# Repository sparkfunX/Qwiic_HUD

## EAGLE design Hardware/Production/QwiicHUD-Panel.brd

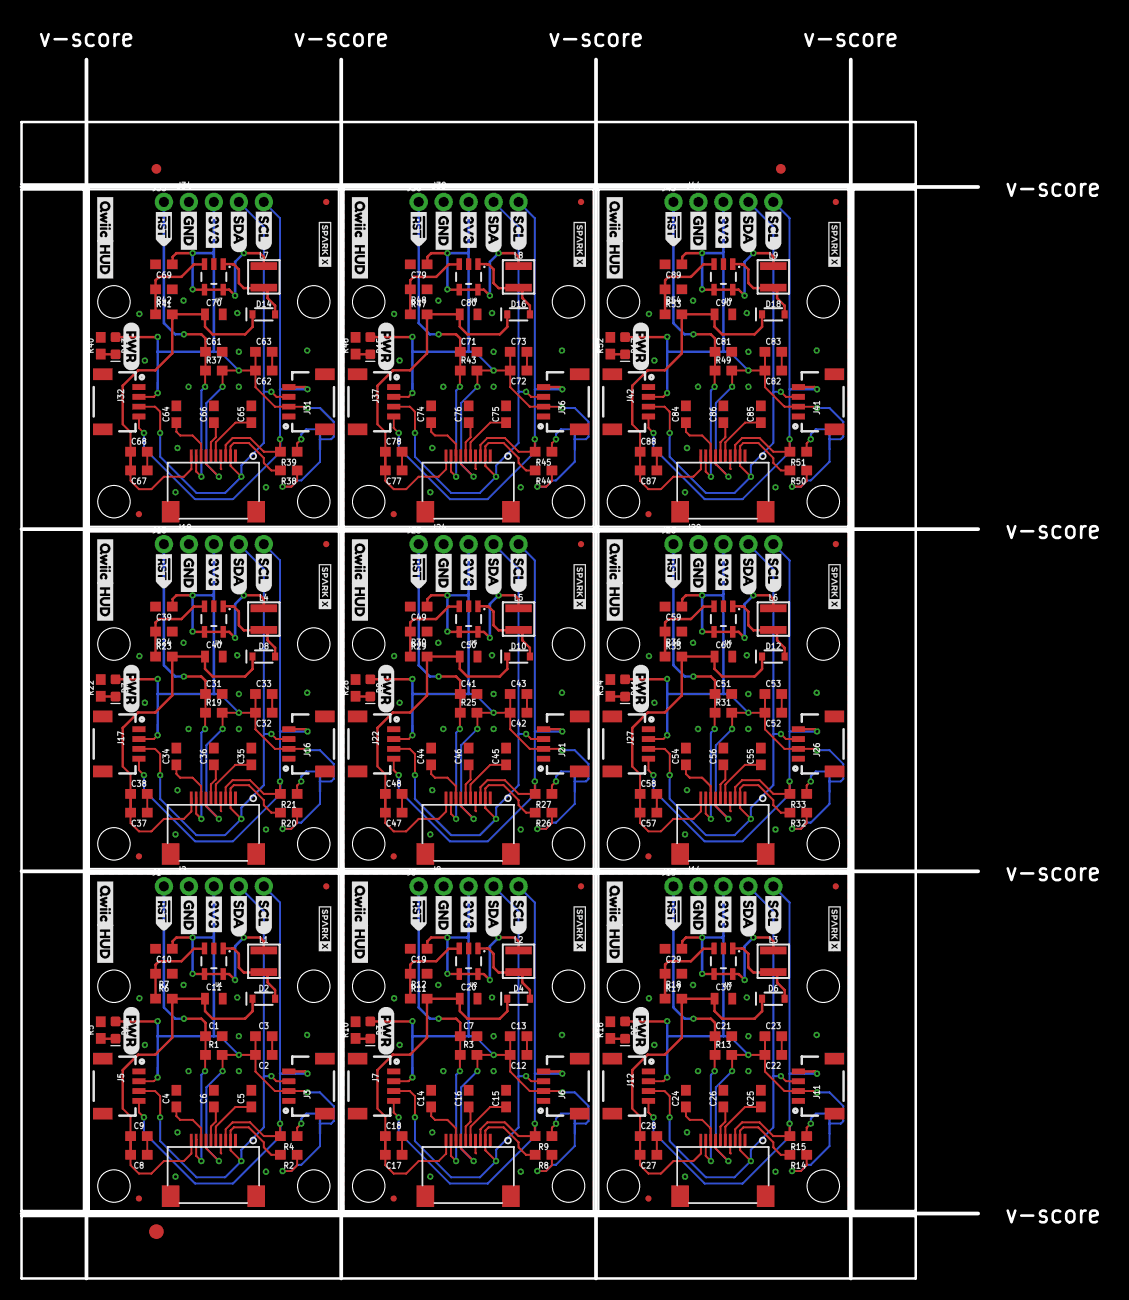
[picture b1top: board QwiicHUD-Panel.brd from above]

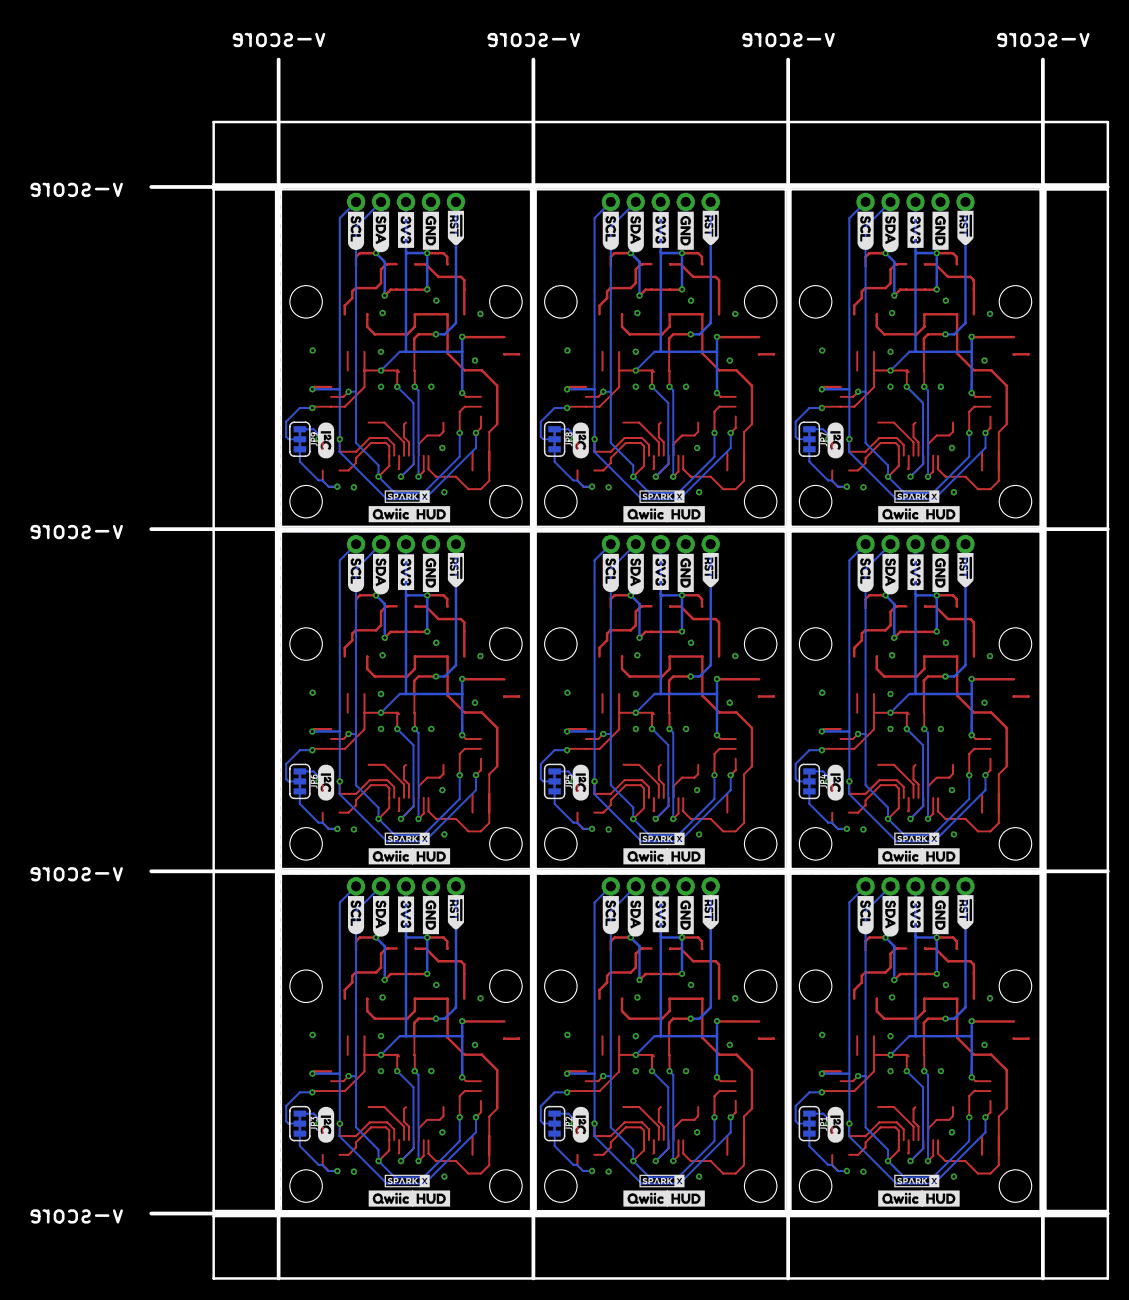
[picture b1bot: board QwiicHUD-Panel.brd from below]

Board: 2 copper layers, 110.5 x 127.8 mm, 426 parts (90 on the bottom side), 126 nets.

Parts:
C1, C7, C21, C31, C41, C51, C61, C71, C81: 2.2uF; 0603
C2, C8, C12, C17, C22, C27, C32, C37, C42, C47, C52, C57, C62, C67, C72, C77, C82, C87: 4.7uF; 0603
C3, C9, C13, C18, C23, C28, C33, C38, C43, C48, C53, C58, C63, C68, C73, C78, C83, C88: 0.1uF; 0603
C4, C5, C6, C10, C14, C15, C16, C19, C24, C25, C26, C29, C34, C35, C36, C39, C44, C45, C46, C49, C54, C55, C56, C59, C64, C65, C66, C69, C74, C75, C76, C79, C84, C85, C86, C89: 1.0uF; 0603
C11, C20, C30, C40, C50, C60, C70, C80, C90: 1.0uF/25V; 0805
D1, D3, D5, D7, D9, D11, D13, D15, D17: RED; LED-0603
D2, D4, D6, D8, D10, D12, D14, D16, D18: 1A/23V/620mV; SOD-323
E$1, E$2: FIDUCIAL-1X2
E$3: FIDUCIAL-1.5X3
FD1, FD2, FD3, FD4, FD5, FD6, FD7, FD8, FD9, FD10, FD11, FD12, FD13, FD14, FD15, FD16, FD17, FD18: FIDUCIALUFIDUCIAL; FIDUCIAL-MICRO
J1, J8, J13, J18, J23, J28, J33, J38, J43: 1X01_NO_SILK
J2, J9, J14, J19, J24, J29, J34, J39, J44: 1X04_NO_SILK
J3, J5, J6, J7, J11, J12, J16, J17, J21, J22, J26, J27, J31, J32, J36, J37, J41, J42: 1X04_1MM_RA
J4, J10, J15, J20, J25, J30, J35, J40, J45: WISECHIP_HUD_FPC; SERIES6288
JP1, JP2, JP3, JP4, JP5, JP6, JP7, JP8, JP9: SMT-JUMPER_3_2-NC_TRACE_SILK
L1, L2, L3, L4, L5, L6, L7, L8, L9: 10uH; INDUCTOR_3X3
R1, R3, R13, R19, R25, R31, R37, R43, R49: 10k; 0603
R2, R4, R8, R9, R14, R15, R20, R21, R26, R27, R32, R33, R38, R39, R44, R45, R50, R51: 2.2k; 0603
R5, R10, R16, R22, R28, R34, R40, R46, R52: 1k; 0603
R6, R11, R17, R23, R29, R35, R41, R47, R53: 47k; 0603
R7, R12, R18, R24, R30, R36, R42, R48, R54: 5.6k; 0603
U1, U2, U3, U4, U5, U6, U7, U8, U9: AP3012; SOT23-5
U$1, U$14, U$23, U$33, U$42, U$52, U$61, U$71, U$80, U$90, U$99, U$109, U$118, U$128, U$137, U$147, U$156, U$166: #RST>
U$2, U$15, U$39, U$58, U$77, U$96, U$115, U$134, U$153: QWIIC_BOARD_OUTLINEH; QWIIC_BOARD_MOUNT_HOLES
U$3, U$4, U$21, U$22, U$40, U$41, U$59, U$60, U$78, U$79, U$97, U$98, U$116, U$117, U$135, U$136, U$154, U$155: SPARKX-TINY
U$5, U$13, U$24, U$32, U$43, U$51, U$62, U$70, U$81, U$89, U$100, U$108, U$119, U$127, U$138, U$146, U$157, U$165: GND
U$6, U$12, U$25, U$31, U$44, U$50, U$63, U$69, U$82, U$88, U$101, U$107, U$120, U$126, U$139, U$145, U$158, U$164: 3V3
U$7, U$10, U$26, U$29, U$45, U$48, U$64, U$67, U$83, U$86, U$102, U$105, U$121, U$124, U$140, U$143, U$159, U$162: SDA
U$8, U$11, U$27, U$30, U$46, U$49, U$65, U$68, U$84, U$87, U$103, U$106, U$122, U$125, U$141, U$144, U$160, U$163: SCL
U$9, U$28, U$47, U$66, U$85, U$104, U$123, U$142, U$161: (PWR)
U$16, U$18, U$34, U$36, U$53, U$55, U$72, U$74, U$91, U$93, U$110, U$112, U$129, U$131, U$148, U$150, U$167, U$169: QWIIC0
U$17, U$19, U$35, U$37, U$54, U$56, U$73, U$75, U$92, U$94, U$111, U$113, U$130, U$132, U$149, U$151, U$168, U$170: HUD1
U$20, U$38, U$57, U$76, U$95, U$114, U$133, U$152, U$171: (I_SUPER2_C)

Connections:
3.3V: C2.2, C3.1, C10.1, D1.A, J2.2, J3.2, J4.4, J5.2, JP1.2, L1.P$1, R1.2, U1.4, U1.5
3.3V1: C12.2, C13.1, C19.1, D3.A, J6.2, J7.2, J9.2, J10.4, JP2.2, L2.P$1, R3.2, U2.4, U2.5
3.3V2: C22.2, C23.1, C29.1, D5.A, J11.2, J12.2, J14.2, J15.4, JP3.2, L3.P$1, R13.2, U3.4, U3.5
3.3V3: C32.2, C33.1, C39.1, D7.A, J16.2, J17.2, J19.2, J20.4, JP4.2, L4.P$1, R19.2, U4.4, U4.5
3.3V4: C42.2, C43.1, C49.1, D9.A, J21.2, J22.2, J24.2, J25.4, JP5.2, L5.P$1, R25.2, U5.4, U5.5
3.3V5: C52.2, C53.1, C59.1, D11.A, J26.2, J27.2, J29.2, J30.4, JP6.2, L6.P$1, R31.2, U6.4, U6.5
3.3V6: C62.2, C63.1, C69.1, D13.A, J31.2, J32.2, J34.2, J35.4, JP7.2, L7.P$1, R37.2, U7.4, U7.5
3.3V7: C72.2, C73.1, C79.1, D15.A, J36.2, J37.2, J39.2, J40.4, JP8.2, L8.P$1, R43.2, U8.4, U8.5
3.3V8: C82.2, C83.1, C89.1, D17.A, J41.2, J42.2, J44.2, J45.4, JP9.2, L9.P$1, R49.2, U9.4, U9.5
12V: C8.2, C9.1, C11.1, D2.C, J4.1, R6.2
12V1: C17.2, C18.1, C20.1, D4.C, J10.1, R11.2
12V2: C27.2, C28.1, C30.1, D6.C, J15.1, R17.2
12V3: C37.2, C38.1, C40.1, D8.C, J20.1, R23.2
12V4: C47.2, C48.1, C50.1, D10.C, J25.1, R29.2
12V5: C57.2, C58.1, C60.1, D12.C, J30.1, R35.2
12V6: C67.2, C68.1, C70.1, D14.C, J35.1, R41.2
12V7: C77.2, C78.1, C80.1, D16.C, J40.1, R47.2
12V8: C87.2, C88.1, C90.1, D18.C, J45.1, R53.2
!RST: C1.1, J1.1, J4.2, R1.1
!RST1: C7.1, J8.1, J10.2, R3.1
!RST2: C21.1, J13.1, J15.2, R13.1
!RST3: C31.1, J18.1, J20.2, R19.1
!RST4: C41.1, J23.1, J25.2, R25.1
!RST5: C51.1, J28.1, J30.2, R31.1
!RST6: C61.1, J33.1, J35.2, R37.1
!RST7: C71.1, J38.1, J40.2, R43.1
!RST8: C81.1, J43.1, J45.2, R49.1
GND: C1.2, C2.1, C3.2, C4.2, C5.2, C6.2, C8.1, C9.2, C10.2, C11.2, J2.1, J3.1, J4.7, J4.10, J5.1, R5.2, R7.1, U1.2
GND1: C7.2, C12.1, C13.2, C14.2, C15.2, C16.2, C17.1, C18.2, C19.2, C20.2, J6.1, J7.1, J9.1, J10.7, J10.10, R10.2, R12.1, U2.2
GND2: C21.2, C22.1, C23.2, C24.2, C25.2, C26.2, C27.1, C28.2, C29.2, C30.2, J11.1, J12.1, J14.1, J15.7, J15.10, R16.2, R18.1, U3.2
GND3: C31.2, C32.1, C33.2, C34.2, C35.2, C36.2, C37.1, C38.2, C39.2, C40.2, J16.1, J17.1, J19.1, J20.7, J20.10, R22.2, R24.1, U4.2
GND4: C41.2, C42.1, C43.2, C44.2, C45.2, C46.2, C47.1, C48.2, C49.2, C50.2, J21.1, J22.1, J24.1, J25.7, J25.10, R28.2, R30.1, U5.2
GND5: C51.2, C52.1, C53.2, C54.2, C55.2, C56.2, C57.1, C58.2, C59.2, C60.2, J26.1, J27.1, J29.1, J30.7, J30.10, R34.2, R36.1, U6.2
GND6: C61.2, C62.1, C63.2, C64.2, C65.2, C66.2, C67.1, C68.2, C69.2, C70.2, J31.1, J32.1, J34.1, J35.7, J35.10, R40.2, R42.1, U7.2
GND7: C71.2, C72.1, C73.2, C74.2, C75.2, C76.2, C77.1, C78.2, C79.2, C80.2, J36.1, J37.1, J39.1, J40.7, J40.10, R46.2, R48.1, U8.2
GND8: C81.2, C82.1, C83.2, C84.2, C85.2, C86.2, C87.1, C88.2, C89.2, C90.2, J41.1, J42.1, J44.1, J45.7, J45.10, R52.2, R54.1, U9.2
IC1: C6.1, J4.5
IC2: C5.1, J4.6
IC3: C4.1, J4.3
IC4: C14.1, J10.3
IC5: C16.1, J10.5
IC6: C15.1, J10.6
IC7: C24.1, J15.3
IC8: C26.1, J15.5
IC9: C25.1, J15.6
IC10: C34.1, J20.3
IC11: C36.1, J20.5
IC12: C35.1, J20.6
IC13: C44.1, J25.3
IC14: C46.1, J25.5
IC15: C45.1, J25.6
IC16: C54.1, J30.3
IC17: C56.1, J30.5
IC18: C55.1, J30.6
IC19: C64.1, J35.3
IC20: C66.1, J35.5
IC21: C65.1, J35.6
IC22: C74.1, J40.3
IC23: C76.1, J40.5
IC24: C75.1, J40.6
IC25: C84.1, J45.3
IC26: C86.1, J45.5
IC27: C85.1, J45.6
unnamed: JP1.3, R2.1
unnamed: JP1.1, R4.1
unnamed: D1.C, R5.1
unnamed: D2.A, L1.P$2, U1.1
unnamed: R6.1, R7.2, U1.3
unnamed: JP2.3, R8.1
unnamed: JP2.1, R9.1
unnamed: D3.C, R10.1
unnamed: D4.A, L2.P$2, U2.1
unnamed: R11.1, R12.2, U2.3
unnamed: JP3.3, R14.1
unnamed: JP3.1, R15.1
unnamed: D5.C, R16.1
unnamed: D6.A, L3.P$2, U3.1
unnamed: R17.1, R18.2, U3.3
unnamed: JP4.3, R20.1
unnamed: JP4.1, R21.1
unnamed: D7.C, R22.1
unnamed: D8.A, L4.P$2, U4.1
unnamed: R23.1, R24.2, U4.3
unnamed: JP5.3, R26.1
unnamed: JP5.1, R27.1
unnamed: D9.C, R28.1
unnamed: D10.A, L5.P$2, U5.1
unnamed: R29.1, R30.2, U5.3
unnamed: JP6.3, R32.1
unnamed: JP6.1, R33.1
unnamed: D11.C, R34.1
unnamed: D12.A, L6.P$2, U6.1
unnamed: R35.1, R36.2, U6.3
unnamed: JP7.3, R38.1
unnamed: JP7.1, R39.1
unnamed: D13.C, R40.1
unnamed: D14.A, L7.P$2, U7.1
unnamed: R41.1, R42.2, U7.3
unnamed: JP8.3, R44.1
unnamed: JP8.1, R45.1
unnamed: D15.C, R46.1
unnamed: D16.A, L8.P$2, U8.1
unnamed: R47.1, R48.2, U8.3
unnamed: JP9.3, R50.1
unnamed: JP9.1, R51.1
unnamed: D17.C, R52.1
unnamed: D18.A, L9.P$2, U9.1
unnamed: R53.1, R54.2, U9.3
SCL: J2.4, J3.4, J4.8, J5.4, R4.2
SCL1: J6.4, J7.4, J9.4, J10.8, R9.2
SCL2: J11.4, J12.4, J14.4, J15.8, R15.2
SCL3: J16.4, J17.4, J19.4, J20.8, R21.2
SCL4: J21.4, J22.4, J24.4, J25.8, R27.2
SCL5: J26.4, J27.4, J29.4, J30.8, R33.2
SCL6: J31.4, J32.4, J34.4, J35.8, R39.2
SCL7: J36.4, J37.4, J39.4, J40.8, R45.2
SCL8: J41.4, J42.4, J44.4, J45.8, R51.2
SDA: J2.3, J3.3, J4.9, J5.3, R2.2
SDA1: J6.3, J7.3, J9.3, J10.9, R8.2
SDA2: J11.3, J12.3, J14.3, J15.9, R14.2
SDA3: J16.3, J17.3, J19.3, J20.9, R20.2
SDA4: J21.3, J22.3, J24.3, J25.9, R26.2
SDA5: J26.3, J27.3, J29.3, J30.9, R32.2
SDA6: J31.3, J32.3, J34.3, J35.9, R38.2
SDA7: J36.3, J37.3, J39.3, J40.9, R44.2
SDA8: J41.3, J42.3, J44.3, J45.9, R50.2

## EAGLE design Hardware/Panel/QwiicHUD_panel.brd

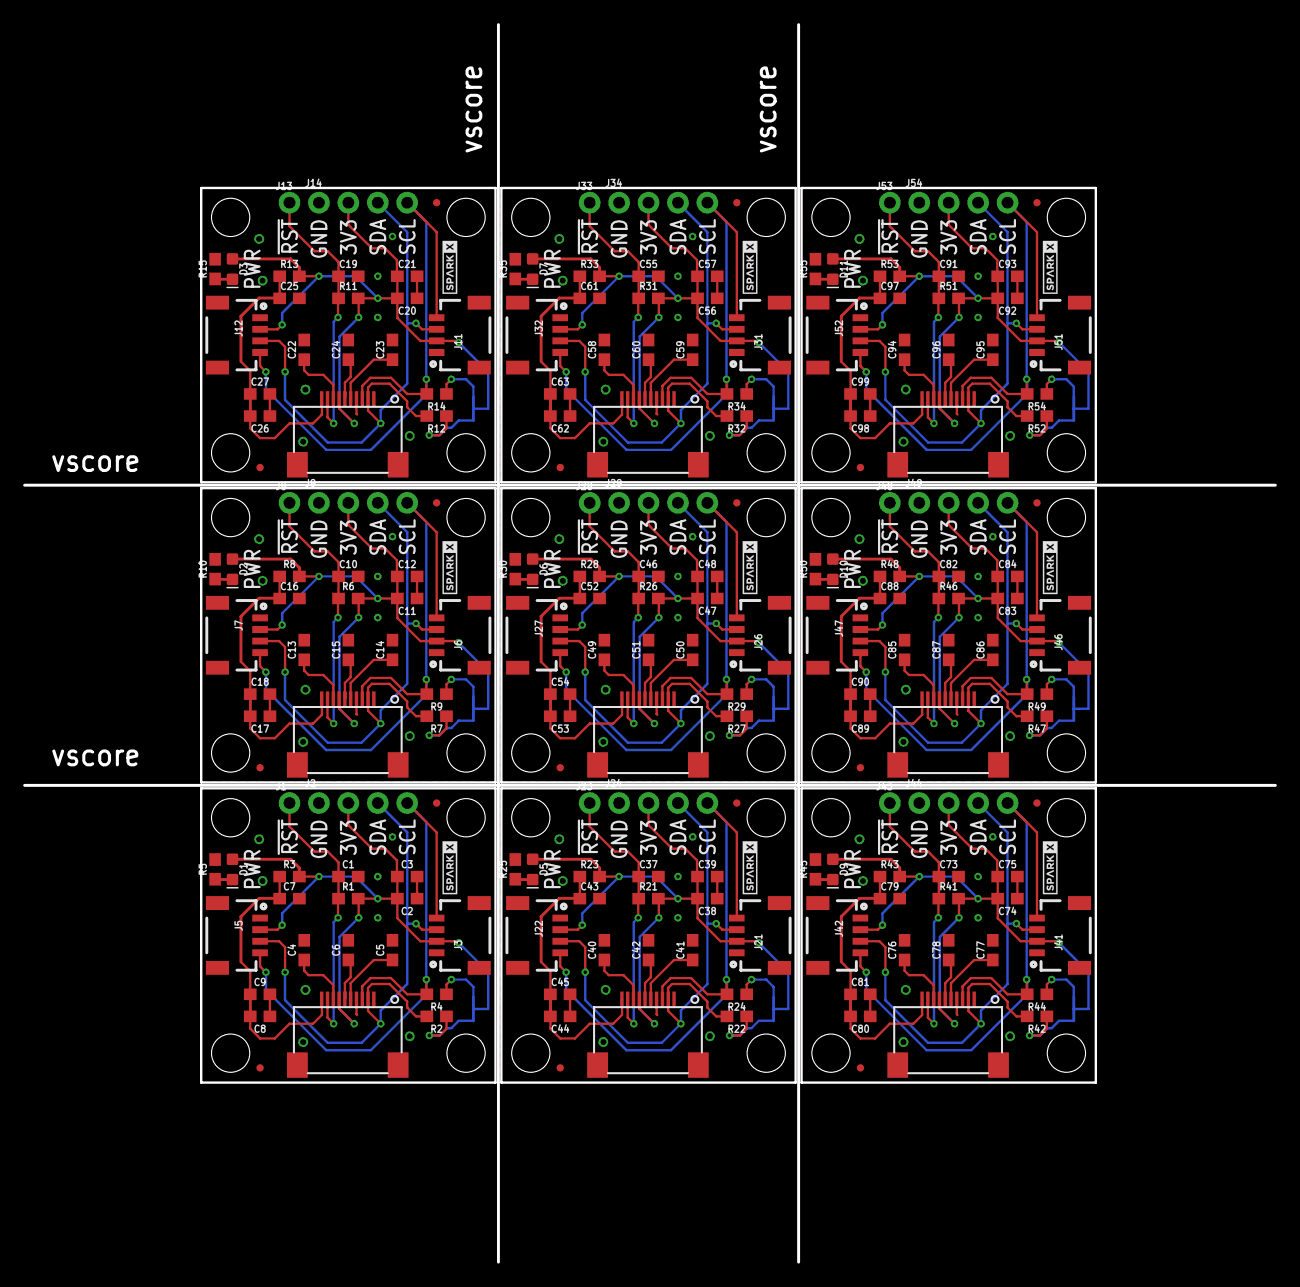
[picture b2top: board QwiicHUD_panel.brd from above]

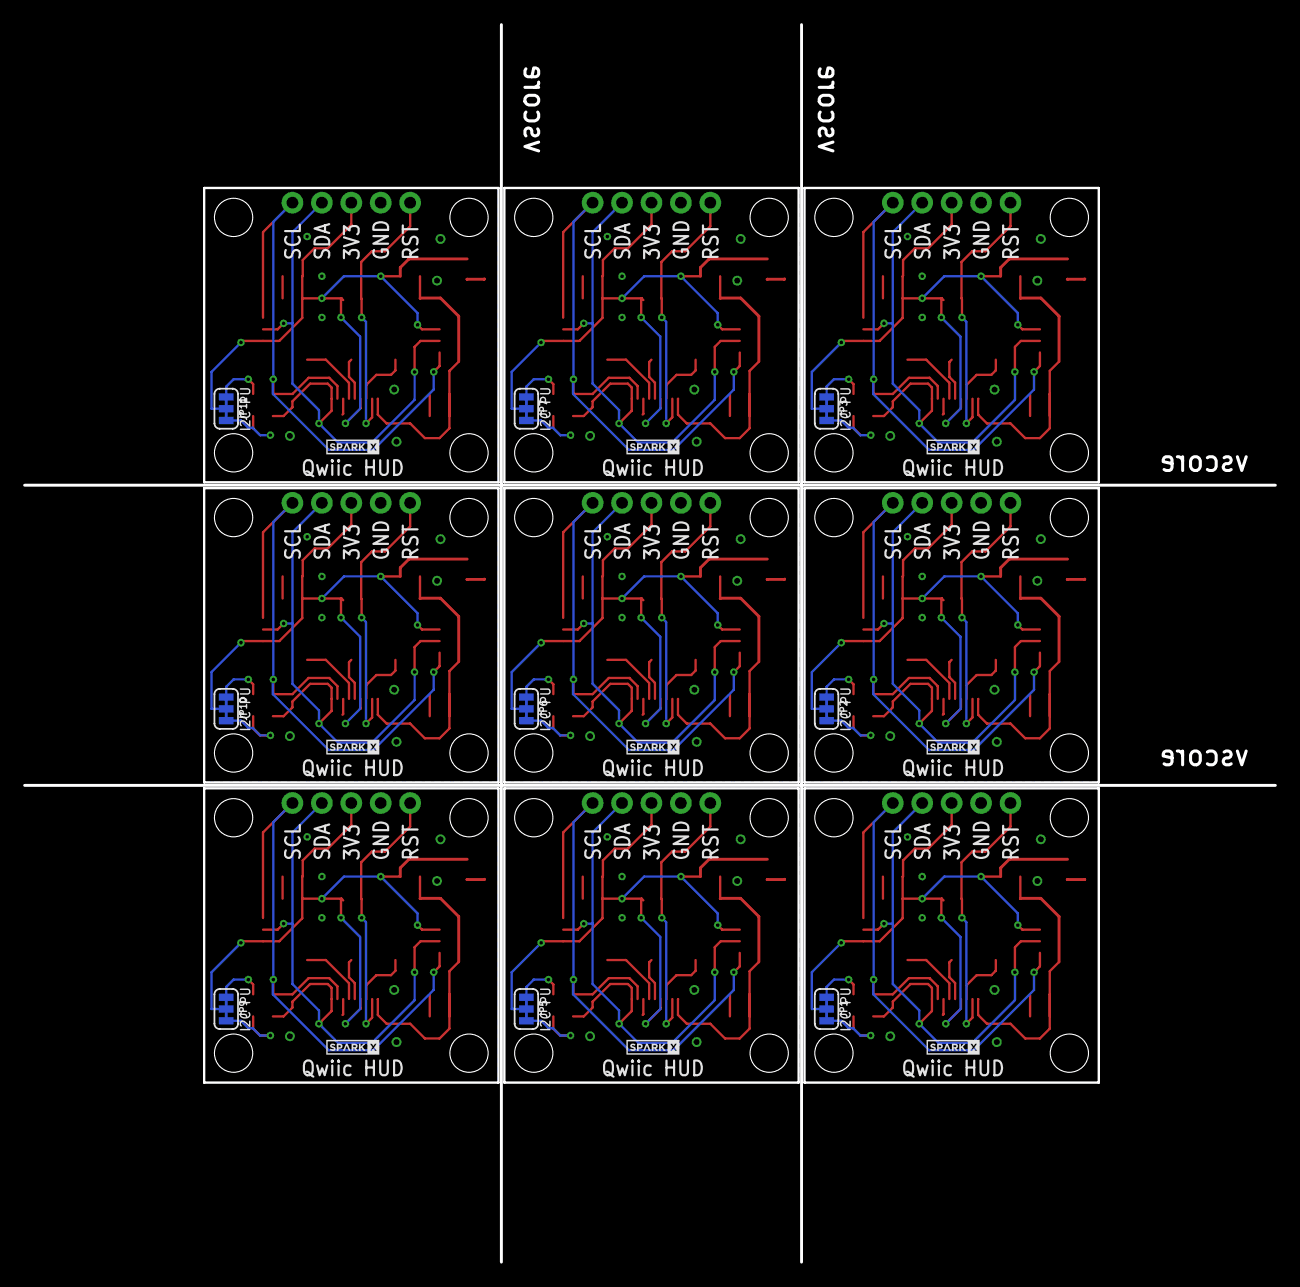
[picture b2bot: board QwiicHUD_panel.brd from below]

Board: 2 copper layers, 107.9 x 106.8 mm, 234 parts (18 on the bottom side), 108 nets.

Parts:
C1, C7, C10, C16, C19, C25, C37, C43, C46, C52, C55, C61, C73, C79, C82, C88, C91, C97: 2.2uF; 0603
C2, C8, C11, C17, C20, C26, C38, C44, C47, C53, C56, C62, C74, C80, C83, C89, C92, C98: 4.7uF; 0603
C3, C9, C12, C18, C21, C27, C39, C45, C48, C54, C57, C63, C75, C81, C84, C90, C93, C99: 0.1uF; 0603
C4, C5, C6, C13, C14, C15, C22, C23, C24, C40, C41, C42, C49, C50, C51, C58, C59, C60, C76, C77, C78, C85, C86, C87, C94, C95, C96: 1.0uF; 0603
D1, D2, D3, D5, D6, D7, D9, D10, D11: RED; LED-0603
FD1, FD2, FD3, FD4, FD5, FD6, FD9, FD10, FD11, FD12, FD13, FD14, FD17, FD18, FD19, FD20, FD21, FD22: FIDUCIALUFIDUCIAL; FIDUCIAL-MICRO
J1, J8, J13, J23, J28, J33, J43, J48, J53: 1X01_NO_SILK
J2, J9, J14, J24, J29, J34, J44, J49, J54: 1X04_NO_SILK
J3, J5, J6, J7, J11, J12, J21, J22, J26, J27, J31, J32, J41, J42, J46, J47, J51, J52: 1X04_1MM_RA
J4, J10, J15, J25, J30, J35, J45, J50, J55: WISECHIP_HUD_FPC; SERIES6288
JP1, JP2, JP3, JP5, JP6, JP7, JP9, JP10, JP11: SMT-JUMPER_3_2-NC_TRACE_SILK
R1, R6, R11, R21, R26, R31, R41, R46, R51: 10k; 0603
R2, R4, R7, R9, R12, R14, R22, R24, R27, R29, R32, R34, R42, R44, R47, R49, R52, R54: 4.7k; 0603
R3, R8, R13, R23, R28, R33, R43, R48, R53: 8.2k; 0603
R5, R10, R15, R25, R30, R35, R45, R50, R55: 1k; 0603
U$1, U$2, U$7, U$13, U$16, U$19, U$25, U$28, U$31: QWIIC_BOARD_OUTLINEH; QWIIC_BOARD_MOUNT_HOLES
U$3, U$4, U$5, U$6, U$8, U$9, U$14, U$15, U$17, U$18, U$20, U$21, U$26, U$27, U$29, U$30, U$32, U$33: SPARKX-TINY

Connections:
3.3V: C2.2, C3.1, D1.A, J2.2, J3.2, J4.4, J5.2, JP1.2, R1.2, R3.2
3.3V1: C11.2, C12.1, D2.A, J6.2, J7.2, J9.2, J10.4, JP2.2, R6.2, R8.2
3.3V2: C20.2, C21.1, D3.A, J11.2, J12.2, J14.2, J15.4, JP3.2, R11.2, R13.2
3.3V4: C38.2, C39.1, D5.A, J21.2, J22.2, J24.2, J25.4, JP5.2, R21.2, R23.2
3.3V5: C47.2, C48.1, D6.A, J26.2, J27.2, J29.2, J30.4, JP6.2, R26.2, R28.2
3.3V6: C56.2, C57.1, D7.A, J31.2, J32.2, J34.2, J35.4, JP7.2, R31.2, R33.2
3.3V8: C74.2, C75.1, D9.A, J41.2, J42.2, J44.2, J45.4, JP9.2, R41.2, R43.2
3.3V9: C83.2, C84.1, D10.A, J46.2, J47.2, J49.2, J50.4, JP10.2, R46.2, R48.2
3.3V10: C92.2, C93.1, D11.A, J51.2, J52.2, J54.2, J55.4, JP11.2, R51.2, R53.2
GND: C1.2, C2.1, C3.2, C4.2, C5.2, C6.2, C7.2, C8.1, C9.2, J2.1, J3.1, J4.7, J4.10, J5.1, R5.2
GND1: C10.2, C11.1, C12.2, C13.2, C14.2, C15.2, C16.2, C17.1, C18.2, J6.1, J7.1, J9.1, J10.7, J10.10, R10.2
GND2: C19.2, C20.1, C21.2, C22.2, C23.2, C24.2, C25.2, C26.1, C27.2, J11.1, J12.1, J14.1, J15.7, J15.10, R15.2
GND4: C37.2, C38.1, C39.2, C40.2, C41.2, C42.2, C43.2, C44.1, C45.2, J21.1, J22.1, J24.1, J25.7, J25.10, R25.2
GND5: C46.2, C47.1, C48.2, C49.2, C50.2, C51.2, C52.2, C53.1, C54.2, J26.1, J27.1, J29.1, J30.7, J30.10, R30.2
GND6: C55.2, C56.1, C57.2, C58.2, C59.2, C60.2, C61.2, C62.1, C63.2, J31.1, J32.1, J34.1, J35.7, J35.10, R35.2
GND8: C73.2, C74.1, C75.2, C76.2, C77.2, C78.2, C79.2, C80.1, C81.2, J41.1, J42.1, J44.1, J45.7, J45.10, R45.2
GND9: C82.2, C83.1, C84.2, C85.2, C86.2, C87.2, C88.2, C89.1, C90.2, J46.1, J47.1, J49.1, J50.7, J50.10, R50.2
GND10: C91.2, C92.1, C93.2, C94.2, C95.2, C96.2, C97.2, C98.1, C99.2, J51.1, J52.1, J54.1, J55.7, J55.10, R55.2
IC1: C6.1, J4.5
IC2: C5.1, J4.6
IC3: C4.1, J4.3
IC4: C13.1, J10.3
IC5: C15.1, J10.5
IC6: C14.1, J10.6
IC7: C22.1, J15.3
IC8: C24.1, J15.5
IC9: C23.1, J15.6
IC13: C40.1, J25.3
IC14: C42.1, J25.5
IC15: C41.1, J25.6
IC16: C49.1, J30.3
IC17: C51.1, J30.5
IC18: C50.1, J30.6
IC19: C58.1, J35.3
IC20: C60.1, J35.5
IC21: C59.1, J35.6
IC25: C76.1, J45.3
IC26: C78.1, J45.5
IC27: C77.1, J45.6
IC28: C85.1, J50.3
IC29: C87.1, J50.5
IC30: C86.1, J50.6
IC31: C94.1, J55.3
IC32: C96.1, J55.5
IC33: C95.1, J55.6
unnamed: JP1.3, R2.1
unnamed: JP1.1, R4.1
unnamed: D1.C, R5.1
unnamed: JP2.3, R7.1
unnamed: JP2.1, R9.1
unnamed: D2.C, R10.1
unnamed: JP3.3, R12.1
unnamed: JP3.1, R14.1
unnamed: D3.C, R15.1
unnamed: JP5.3, R22.1
unnamed: JP5.1, R24.1
unnamed: D5.C, R25.1
unnamed: JP6.3, R27.1
unnamed: JP6.1, R29.1
unnamed: D6.C, R30.1
unnamed: JP7.3, R32.1
unnamed: JP7.1, R34.1
unnamed: D7.C, R35.1
unnamed: JP9.3, R42.1
unnamed: JP9.1, R44.1
unnamed: D9.C, R45.1
unnamed: JP10.3, R47.1
unnamed: JP10.1, R49.1
unnamed: D10.C, R50.1
unnamed: JP11.3, R52.1
unnamed: JP11.1, R54.1
unnamed: D11.C, R55.1
RST: C1.1, J1.1, J4.2, R1.1
RST1: C10.1, J8.1, J10.2, R6.1
RST2: C19.1, J13.1, J15.2, R11.1
RST4: C37.1, J23.1, J25.2, R21.1
RST5: C46.1, J28.1, J30.2, R26.1
RST6: C55.1, J33.1, J35.2, R31.1
RST8: C73.1, J43.1, J45.2, R41.1
RST9: C82.1, J48.1, J50.2, R46.1
RST10: C91.1, J53.1, J55.2, R51.1
SCL: J2.4, J3.4, J4.8, J5.4, R4.2
SCL1: J6.4, J7.4, J9.4, J10.8, R9.2
SCL2: J11.4, J12.4, J14.4, J15.8, R14.2
SCL4: J21.4, J22.4, J24.4, J25.8, R24.2
SCL5: J26.4, J27.4, J29.4, J30.8, R29.2
SCL6: J31.4, J32.4, J34.4, J35.8, R34.2
SCL8: J41.4, J42.4, J44.4, J45.8, R44.2
SCL9: J46.4, J47.4, J49.4, J50.8, R49.2
SCL10: J51.4, J52.4, J54.4, J55.8, R54.2
SDA: J2.3, J3.3, J4.9, J5.3, R2.2
SDA1: J6.3, J7.3, J9.3, J10.9, R7.2
SDA2: J11.3, J12.3, J14.3, J15.9, R12.2
SDA4: J21.3, J22.3, J24.3, J25.9, R22.2
SDA5: J26.3, J27.3, J29.3, J30.9, R27.2
SDA6: J31.3, J32.3, J34.3, J35.9, R32.2
SDA8: J41.3, J42.3, J44.3, J45.9, R42.2
SDA9: J46.3, J47.3, J49.3, J50.9, R47.2
SDA10: J51.3, J52.3, J54.3, J55.9, R52.2
VCC: C7.1, C8.2, C9.1, J4.1, R3.1
VCC1: C16.1, C17.2, C18.1, J10.1, R8.1
VCC2: C25.1, C26.2, C27.1, J15.1, R13.1
VCC4: C43.1, C44.2, C45.1, J25.1, R23.1
VCC5: C52.1, C53.2, C54.1, J30.1, R28.1
VCC6: C61.1, C62.2, C63.1, J35.1, R33.1
VCC8: C79.1, C80.2, C81.1, J45.1, R43.1
VCC9: C88.1, C89.2, C90.1, J50.1, R48.1
VCC10: C97.1, C98.2, C99.1, J55.1, R53.1

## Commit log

2018-04-13 x02
    Added 12V boost circuit
2018-04-20 Cleaning Up
2018-04-20 Adding a PDF of the schematic
2018-08-29 Changed inductor to inventory part
2018-08-30 Revert "Create README.md"
    This reverts commit a325ca2dac4d20ebcfd2de1912729ced435e2176.
2018-08-30 Revert "Changed inductor to inventory part"
    This reverts commit 6ab7a03f3320a090153a192dfaf0fd3f0c8c93f1.

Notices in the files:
parts and their libraries:
SparkFun-Capacitors: Licensing: Creative Commons ShareAlike 4.0 International - https://creativecommons.org/licenses/by-sa/4.0
